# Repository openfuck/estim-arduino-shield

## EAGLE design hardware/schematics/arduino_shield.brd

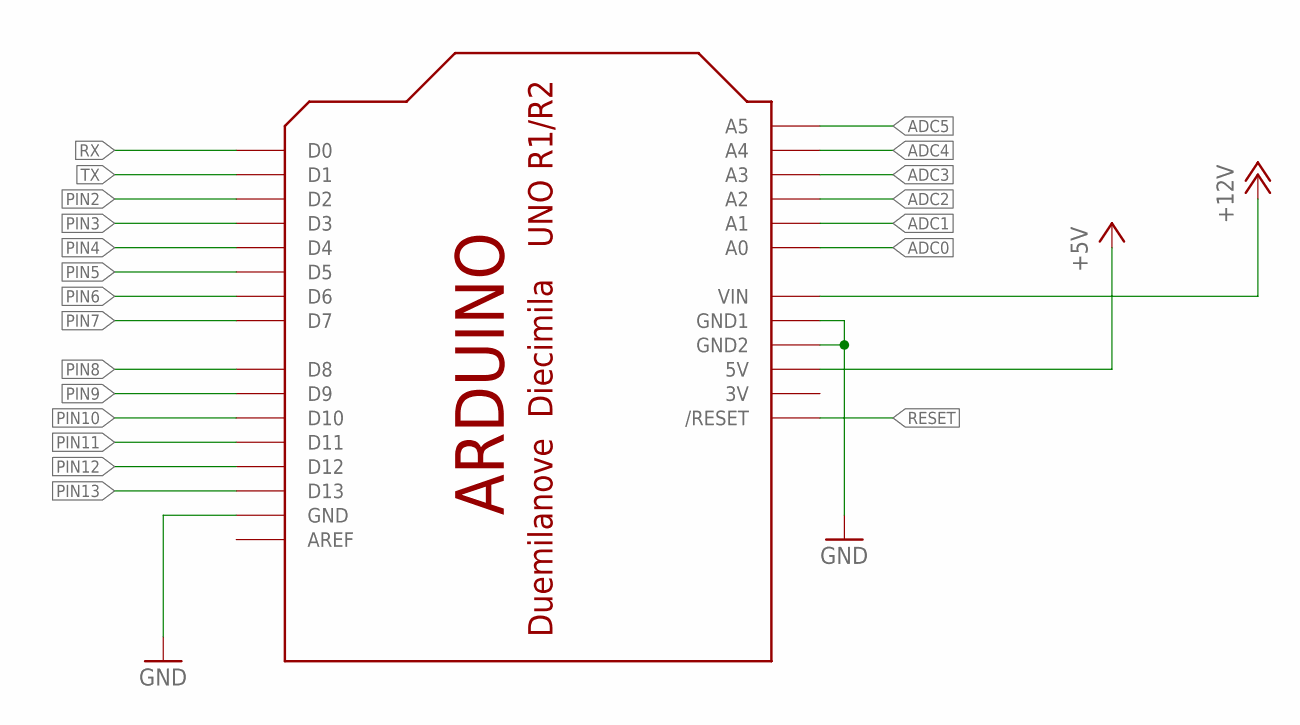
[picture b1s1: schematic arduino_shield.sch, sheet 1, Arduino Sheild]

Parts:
GND: ARDUINOUNO; ARDUINO

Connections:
3V: GND.3V
+5V: GND.5V; also elsewhere on the board
+12V: GND.VIN; also elsewhere on the board
ADC0: GND.A0
ADC1: GND.A1; also elsewhere on the board
ADC2: GND.A2
ADC3: GND.A3
ADC4: GND.A4
ADC5: GND.A5
GND: GND.GND, GND.GND1, GND.GND2; also elsewhere on the board
PIN2: GND.D2
PIN3: GND.D3; also elsewhere on the board
PIN4: GND.D4; also elsewhere on the board
PIN5: GND.D5; also elsewhere on the board
PIN6: GND.D6; also elsewhere on the board
PIN7: GND.D7
PIN8: GND.D8
PIN9: GND.D9; also elsewhere on the board
PIN10: GND.D10
PIN11: GND.D11; also elsewhere on the board
PIN12: GND.D12
PIN13: GND.D13; also elsewhere on the board
RESET: GND.RESET (/RESET)
RX: GND.D0
TX: GND.D1

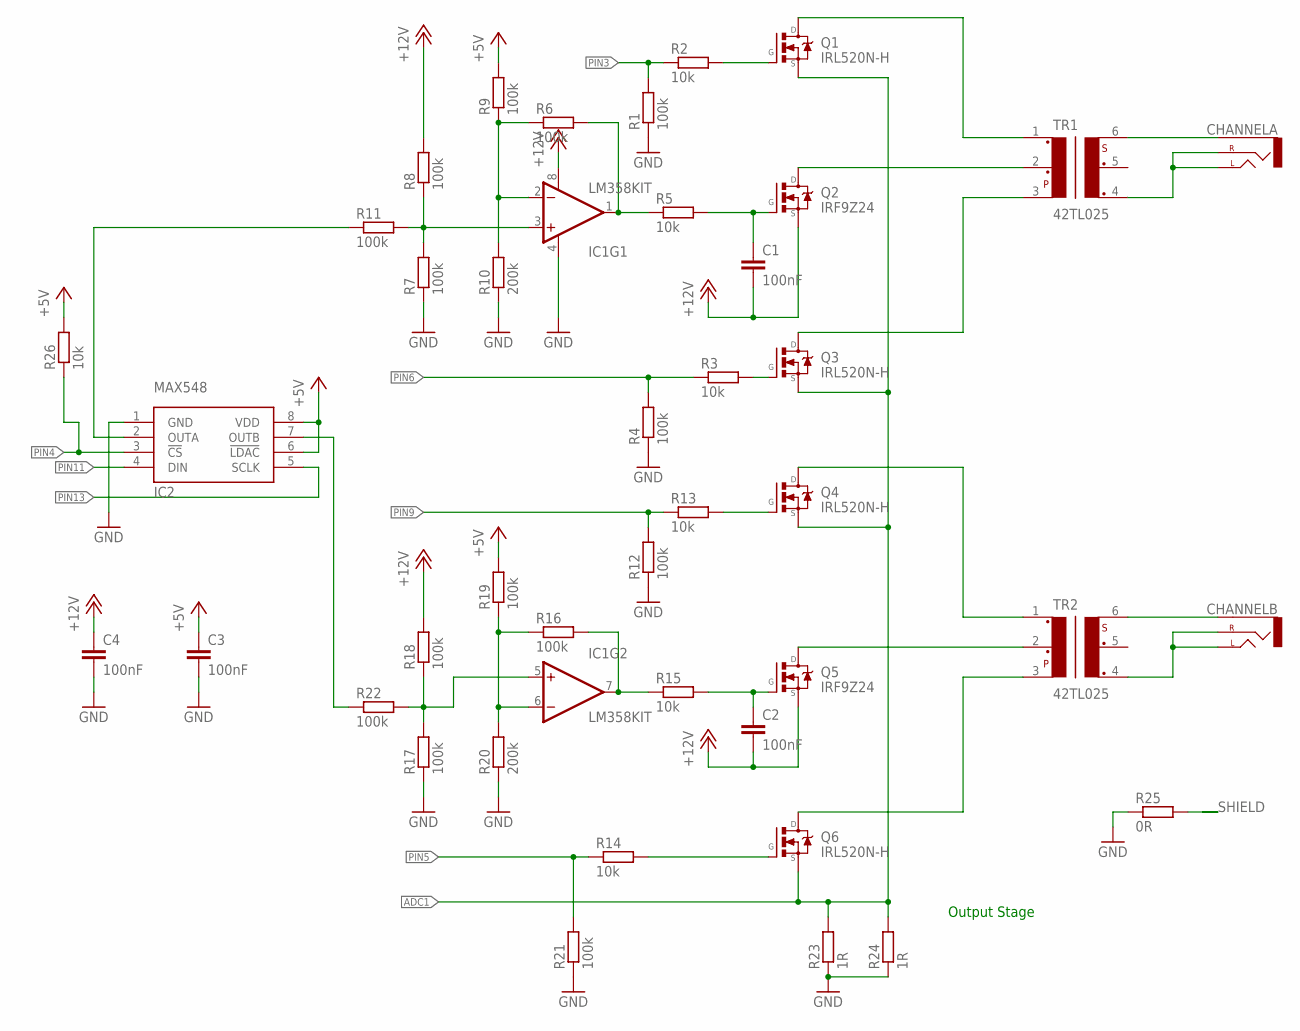
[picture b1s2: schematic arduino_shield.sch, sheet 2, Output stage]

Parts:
C1, C2, C3, C4: 100nF; C2.5-2
CHANNELA: AUDIO-JACK2.5MM; STEREOJACK2.5MM_STEREOJACK2.5MM
CHANNELB: AUDIO-JACK2.5MM; STEREOJACK2.5MM_STEREOJACK2.5MM
IC1: LM358KIT; DIP08-KIT
IC2: MAX548; DIL08
Q1, Q3, Q4, Q6: IRL520N-H; TO220V
Q2, Q5: IRF9Z24; TO220V
R1, R4, R6, R7, R8, R9, R11, R12, R16, R17, R18, R19, R21, R22: 100k; R0805
R2, R3, R5, R13, R14, R15, R26: 10k; R0805
R10, R20: 200k; R0805
R23, R24: 1R; R0805
R25: 0R; R0805
TR1, TR2: 42TL025; 42TL

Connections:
+5V: C3.1, IC2.6 (!LDAC), IC2.8 (VDD), R9.2, R19.2, R26.2; also elsewhere on the board
+12V: C1.2, C2.2, C4.1, IC1.8 (V+), Q2.3 (S), Q5.3 (S), R8.2, R18.2; also elsewhere on the board
ADC1: Q1.3 (S), Q3.3 (S), Q4.3 (S), Q6.3 (S), R23.2, R24.2; also elsewhere on the board
GND: C3.2, C4.2, IC1.4 (V-), IC2.1 (GND), R1.1, R4.1, R7.1, R10.1, R12.1, R17.1, R20.1, R21.1, R23.1, R24.1, R25.1; also elsewhere on the board
unnamed: CHANNELA.RING1 (SLEEVE), TR1.6
unnamed: CHANNELB.RING1 (SLEEVE), TR2.6
unnamed: CHANNELB.SHIELD (LEFT), CHANNELB.TIP (RIGHT), TR2.4
unnamed: CHANNELA.SHIELD (LEFT), CHANNELA.TIP (RIGHT), TR1.4
unnamed: IC2.2 (OUTA), R11.1
unnamed: IC2.7 (OUTB), R22.1
unnamed: Q1.1 (G), R2.2
unnamed: Q3.1 (G), R3.2
unnamed: IC1.1 (OUT), R5.1, R6.2
unnamed: C1.1, Q2.1 (G), R5.2
unnamed: IC1.3 (+IN), R7.2, R8.1, R11.2
unnamed: Q4.1 (G), R13.2
unnamed: Q6.1 (G), R14.2
unnamed: IC1.7 (OUT), R15.1, R16.2
unnamed: C2.1, Q5.1 (G), R15.2
unnamed: IC1.5 (+IN), R17.2, R18.1, R22.2
unnamed: Q1.2 (D), TR1.1
unnamed: Q2.2 (D), TR1.2
unnamed: Q4.2 (D), TR2.1
unnamed: Q5.2 (D), TR2.2
unnamed: Q6.2 (D), TR2.3
unnamed: Q3.2 (D), TR1.3
unnamed: IC1.2 (-IN), R6.1, R9.1, R10.2
unnamed: IC1.6 (-IN), R16.1, R19.1, R20.2
PIN3: R1.2, R2.1; also elsewhere on the board
PIN4: IC2.3 (!CS), R26.1; also elsewhere on the board
PIN5: R14.1, R21.2; also elsewhere on the board
PIN6: R3.1, R4.2; also elsewhere on the board
PIN9: R12.2, R13.1; also elsewhere on the board
PIN11: IC2.4 (DIN); also elsewhere on the board
PIN13: IC2.5 (SCLK); also elsewhere on the board
SHIELD: R25.2

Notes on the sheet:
Output Stage

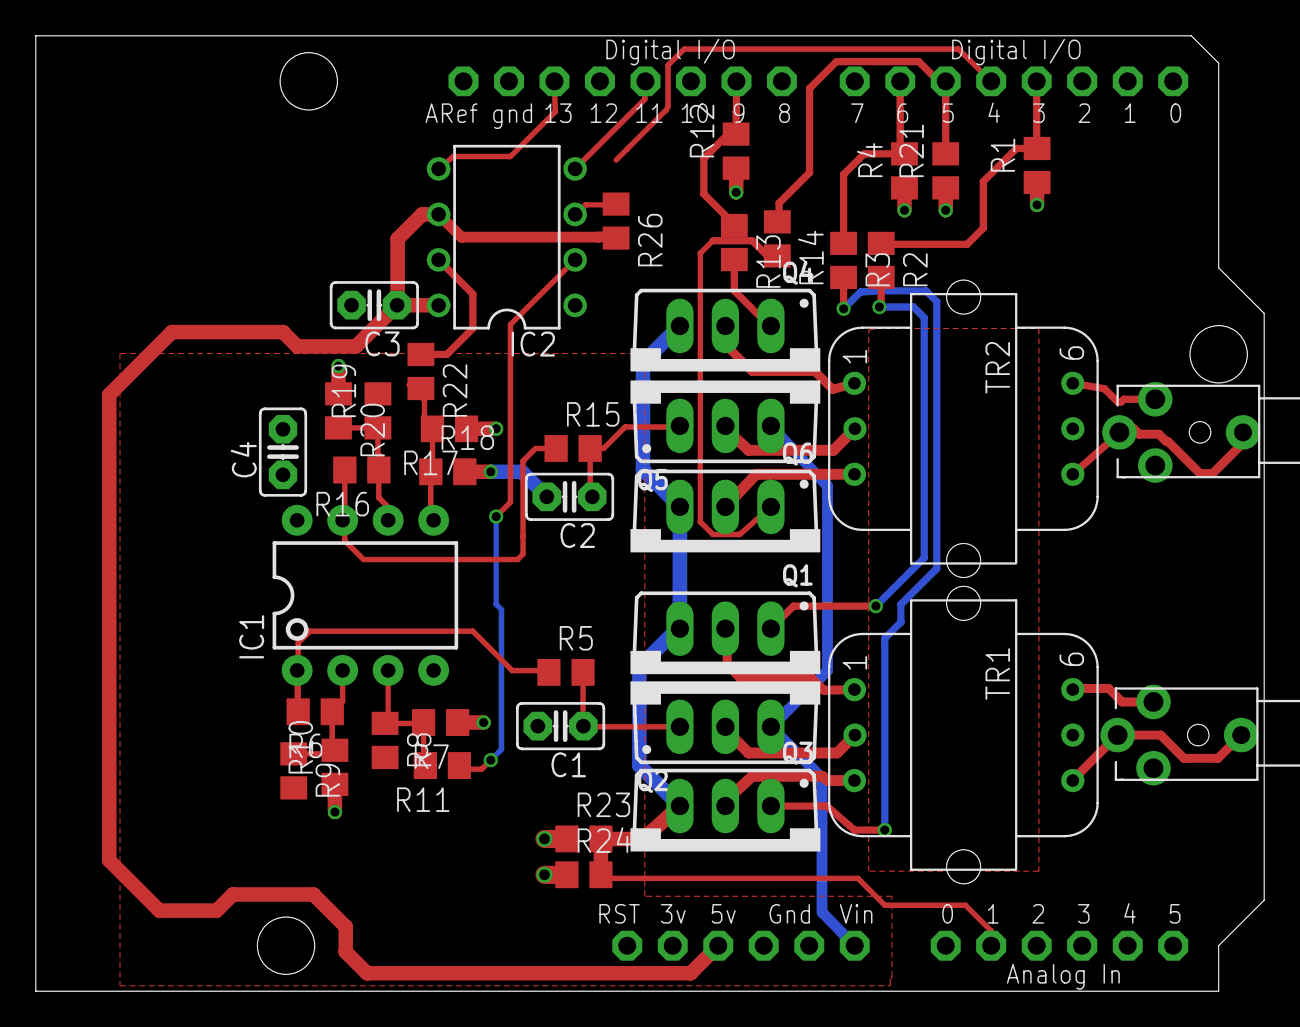
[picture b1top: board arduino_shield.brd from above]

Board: 2 copper layers, 68.6 x 53.3 mm, 43 parts (1 on the bottom side), 35 nets.

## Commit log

2016-07-01 Git Ignore
    Try and keep my mac and eagle files away from teh repository
2016-07-01 Added blank schematic
2016-07-01 Added PDF
    work done on schematic, PDF generated for people who don't have eagle.
2016-07-01 Schematic update
    Added screen, finished buttons
2016-07-01 fixed uC
    picked up a atmega16 rather than atmega8
2016-07-01 CDB4066 added
    Control pins are listed as connected to pin 22 on uC, 22 is listed as a ground… can some one please check!
2016-07-01 Added small board
    Added 2 buttons, and two pots to the small board, found the CD4066 in dip, and added to new sheet.
2016-07-01 PCB WIP
    Layed down uC and some other componants
2016-07-01 moved folder to hardware
2016-07-01 A Lot of work done :D
    Assuming the Transformer is correct, we have a version we can send to a fab house
2016-07-01 Changes by FluffyBit
    done:
    - changed grid to 0.1mm to help place components
    - forced all components onto 0.1mm grid
    - added gnd plane on bottom of board
    - added two caps for decoupling the DAC+OP-AMP
    - added 10K pull-up on the nCS line to the DAC
2016-07-01 Remove old schematics
    Remove old schematics that have had no work on them for a while.
2016-07-01 Snapshot of Eagle files as PDF
    Snapshot of Eagle files as PDF
    because these are binary blobs, will snapshot spairingly.
2016-07-01 cleanup and new pdfs
2016-07-01 Added bom
    Bill of Materials, will use to look up part numbers and costing.
2016-07-01 schematics
2016-07-01 Schematics
    WIP
2016-07-01 nope mcnopeface
2016-07-01 Starting an Arduino Sheild
2016-07-01 Testing to see if resistor networks help
2016-07-01 Arduino Sheild Eagle
2016-07-01 Updates to BOM
2016-07-01 Stop horible things happening with eagle

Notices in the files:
parts and their libraries:
SparkFun-AnalogIC: Licensing:Creative Commons ShareAlike 4.0 International - https://creativecommons.org/licenses/by-sa/4.0
